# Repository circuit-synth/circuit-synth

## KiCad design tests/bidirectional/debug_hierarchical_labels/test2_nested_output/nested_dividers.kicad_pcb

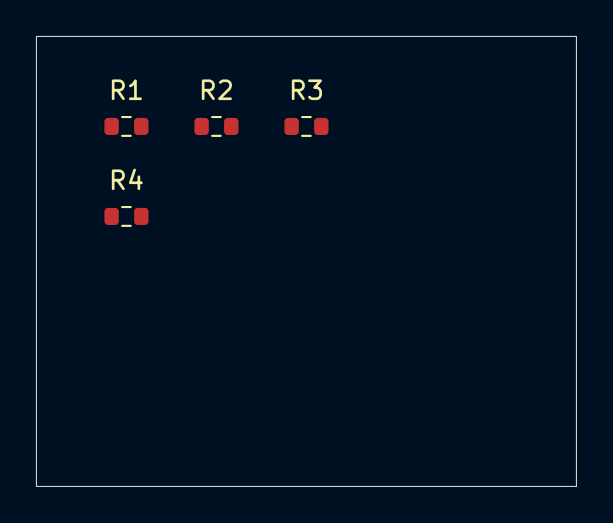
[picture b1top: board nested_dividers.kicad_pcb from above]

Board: 2 copper layers, 30.0 x 25.0 mm, 4 parts (0 on the bottom side), 3 nets, no tracks yet.

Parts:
R1, R2: 10k; R_0603_1608Metric
R3, R4: 5k; R_0603_1608Metric

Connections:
GND: R2.2, R4.2
VOUT1: R1.2, R2.1, R3.1
VOUT2: R3.2, R4.1
